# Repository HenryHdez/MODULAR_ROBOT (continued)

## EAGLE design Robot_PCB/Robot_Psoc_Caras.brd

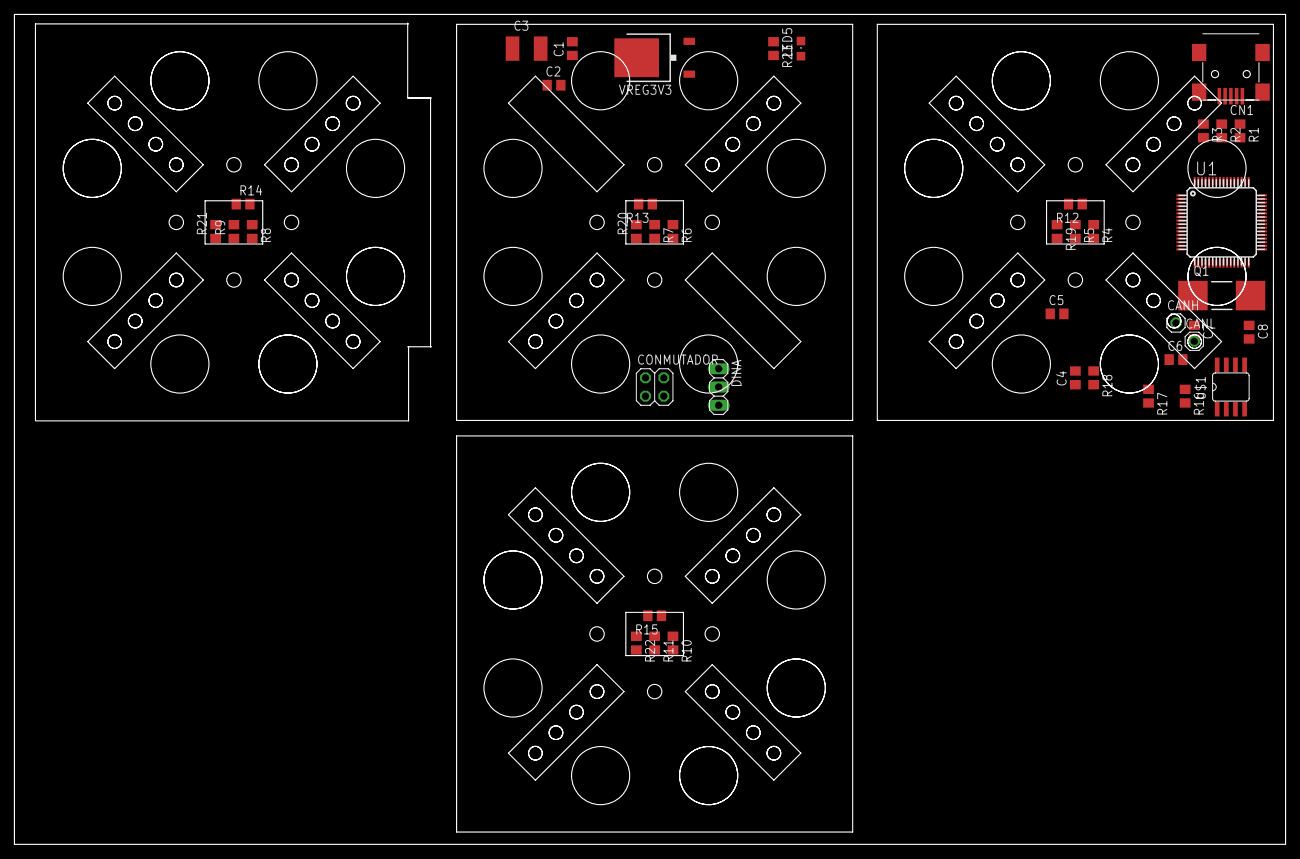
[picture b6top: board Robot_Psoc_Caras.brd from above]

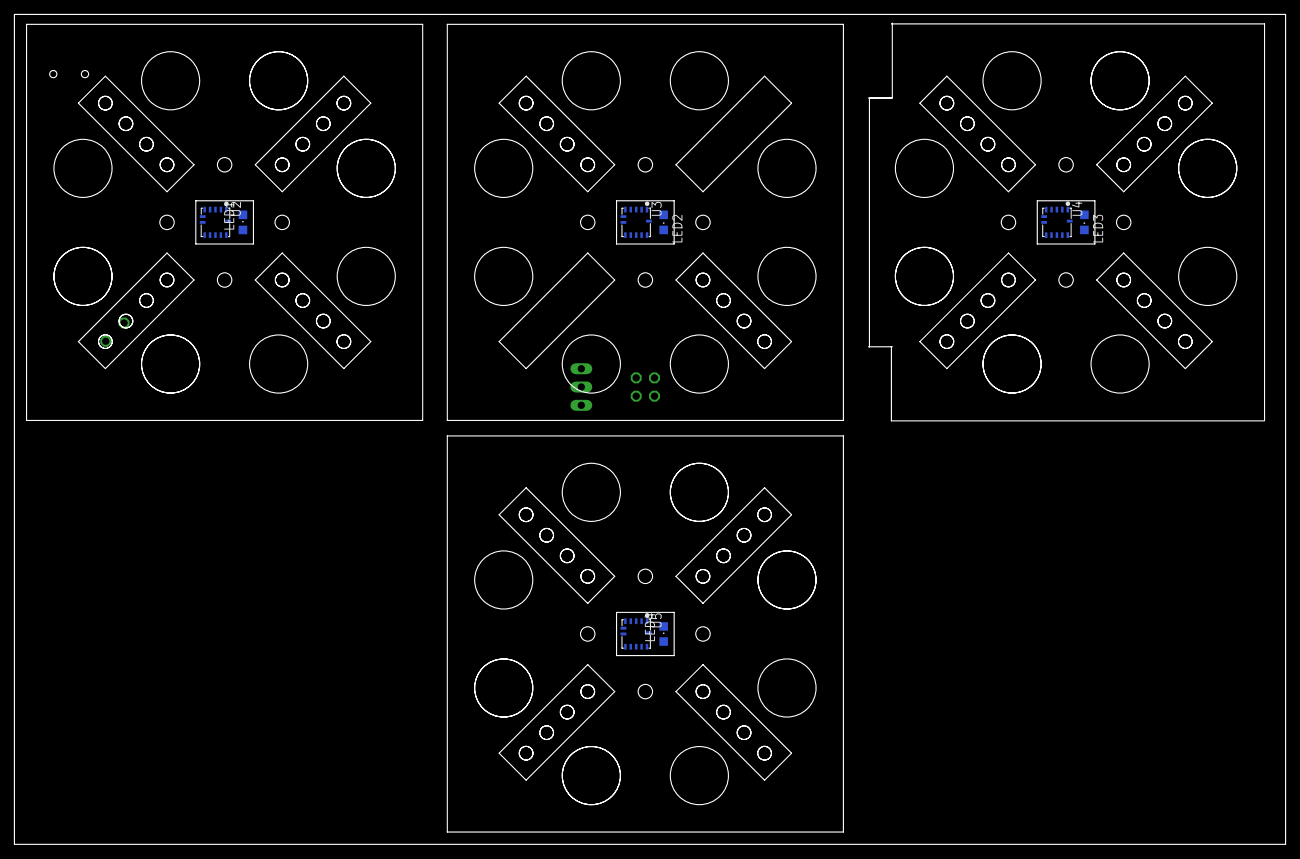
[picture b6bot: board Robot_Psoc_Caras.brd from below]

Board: 2 copper layers, 176.5 x 115.2 mm, 49 parts (8 on the bottom side), 44 nets, no tracks yet.

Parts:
C1, C2, C7, C8: 0.1uF; C0805
C3: 10uF; C4532
C4: 2200pF; C0805
C5: 10nF; C0805
C6: 1u; C0805
CANH: 1X01
CANL: 1X01
CN1: USB-MINIB
CONMUTADOR: 2X02
DINA: 1X03
LED1, LED2, LED3, LED4, LED5: CHIPLED_0805
Q1: MC-405
R1, R2, R3, R18: 0; R0805
R4, R5, R6, R7, R8, R9, R10, R11, R17: 10k; R0805
R12, R13, R14, R15, R19, R20, R21, R22, R23: 220; R0805
R16: 120; R0805
U1: CY8C4247AZI-M485; TQFP64-10X10
U2, U3, U4, U5: VCNL4010-GS08; XDCR_VCNL4010-GS08
U$1: SN65HVD230/1; SO8
VREG3V3: 7824DT; TO252

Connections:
+3V3: C1.1, C2.1, C3.1, CN1.VBUS, LED5.A, R4.2, R5.2, R6.2, R7.2, R8.2, R9.2, R10.2, R11.2, U1.11, U1.26, U1.48, U1.50, U1.56, U2.1, U2.7, U3.1, U3.7, U4.1, U4.7, U5.1, U5.7, U$1.3, VREG3V3.2
+10V: DINA.2, VREG3V3.1
CAN_RX: U1.39, U$1.4
CAN_TX: U1.40, U$1.1
CTANK: C5.1, U1.30
GND: C1.2, C2.2, C3.2, C4.2, C5.2, C6.2, C7.2, C8.2, CN1.D+, DINA.3, R12.2, R13.2, R14.2, R15.2, R17.2, R19.2, R20.2, R21.2, R22.2, R23.2, U1.10, U1.17, U1.49, U1.57, U2.12, U2.13, U3.12, U3.13, U4.12, U4.13, U5.12, U5.13, U$1.2, VREG3V3.3
LED_S1: LED1.A, U1.63
LED_S2: LED2.A, U1.62
LED_S3: LED3.A, U1.61
LED_S4: LED4.A, U1.60
MOTOR: CONMUTADOR.1, U1.13, U1.14
unnamed: CN1.D-, R1.1
unnamed: CN1.ID, R2.1
unnamed: CN1.GND, R3.1
unnamed: R12.1, U2.2, U2.3
unnamed: CONMUTADOR.3, R16.2, U$1.7
unnamed: R13.1, U3.2, U3.3
unnamed: CANL.1, R16.1, U$1.6
unnamed: R14.1, U4.2, U4.3
unnamed: R17.1, U$1.8
unnamed: R15.1, U5.2, U5.3
unnamed: C4.1, R18.2
unnamed: CANH.1, CONMUTADOR.4
unnamed: CONMUTADOR.2, DINA.1
unnamed: LED1.C, R19.1
unnamed: LED2.C, R20.1
unnamed: LED3.C, R21.1
unnamed: LED4.C, R22.1
unnamed: LED5.C, R23.1
SAR_BY: C6.1, U1.1
SCL_S1: R4.1, U1.2, U2.5
SCL_S2: R6.1, U1.4, U3.5
SCL_S3: R8.1, U1.6, U4.5
SCL_S4: R10.1, U1.8, U5.5
SDA_S1: R5.1, U1.3, U2.4
SDA_S2: R7.1, U1.5, U3.4
SDA_S3: R9.1, U4.4
SDA_S4: R11.1, U1.7, U5.4
SHUNT: R18.1, U1.29
SWDCLK: R2.2, U1.21
SWDIO: R3.2, U1.20
X1: C7.1, Q1.1, U1.43
X2: C8.1, Q1.2, U1.44
XRES: R1.2, U1.47

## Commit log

2016-09-27 :neckbeard: Added .gitattributes & .gitignore files
2016-09-27 Init commit
2016-10-19 19 de Octubre de 2016
2016-10-30 30_Oct_2016
    Parcial Changes and Program Probes
2016-11-15 15/11/2016
2017-01-05 5/01/2017
    Add Libraries For modular Robot
2017-01-10 9 de Enero de 2017
    Gerber's Robot and Examples
2017-01-10 10 de Enero de 2017
    Manuales e Indicaciones
2017-01-11 11 de Enero 2017
    Manuals
2017-01-16 15 de Enero de 2017
    Xbee Adapter Agregado
2017-01-16 16 de Enero de 2016
    PCB
2017-02-06 05-Febrero-2017
    CAN Example
2017-04-28 27 Abril 2017
    PCB numero 4
2017-05-02 2-05-2017
    Hoy
2017-05-05 02/May/2017
2017-05-05 05/May
    PCB
2017-05-08 07-May
    PCB_Partido
2017-05-08 8-May
2017-05-08 8_May_2
2017-06-30 29/06/2017
    Gerber
2017-07-17 16/07/2017
2017-08-21 ULTIMA EDICION
2017-08-23 Edicion Diaria
2017-09-25 25-nov
2017-10-18 18_Oct_1017
    Optimization Algoritm OK
2018-01-15 14-ene-18
    At last changes
2018-01-19 18_Ene
    Cambios
2018-01-22 21-Ene
    Cambios
2018-01-22 22/01/2017
    Definitivo
2018-02-05 04/Feb/2018
    Definitivo
2018-11-28 27-Nov
    Ultimas reformas
